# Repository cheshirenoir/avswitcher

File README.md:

# avswitcher
A modular AV Switcher. No scaling. Just switching. SVideo, Composite, Component and RGB (in the form of HD15)

THIS IS IN A VERY EARLY STATE. NOT FIT FOR PRODUCTION

This consists of a "Brainboard" containing an Arduino, A "Bus" that connects the other boards, and has the select logic for choosing which input has been selected, a control board, designed to plug into the front of the brain board. There is a Video out board that contains all the possible outputs, with a mirrored audio pair for each input. This plugs into the back of the Brainboard. It also handles the power in. (It's all designed to run off a 5V input. If I hit problems with power use, and I don't expect to, I can look at switching over to 9v and dropping a 7805 on each output board.) Finally there are the 4 different input boards that can be plugged into the bus, one each for SVideo, Composite, Component and "VGA" (Actually just RGBHV).
Each input board has a digitally controlled switch, which means unless they are selected, they stay isolated. Awesome for keeping the bus quiet when you are using the other input.
Why did I build this? Becauise I accidentally ended up with a collection of consoles, and switching between them was becoming a nightmare of switchers, scalers and general cable mess. I decided I wanted everything plugging into one box, and I could then plug just one scaler into each output.
I am now contemplating adding a relay to each output so I can switch on and off scalers as needed. That will need to wait for a later versions.

I haven't even started writing code for any of this. Talk about putting the horse before the cart.

Thanks to Kaypy for his advice.

Oh erm. CC-BY-SA

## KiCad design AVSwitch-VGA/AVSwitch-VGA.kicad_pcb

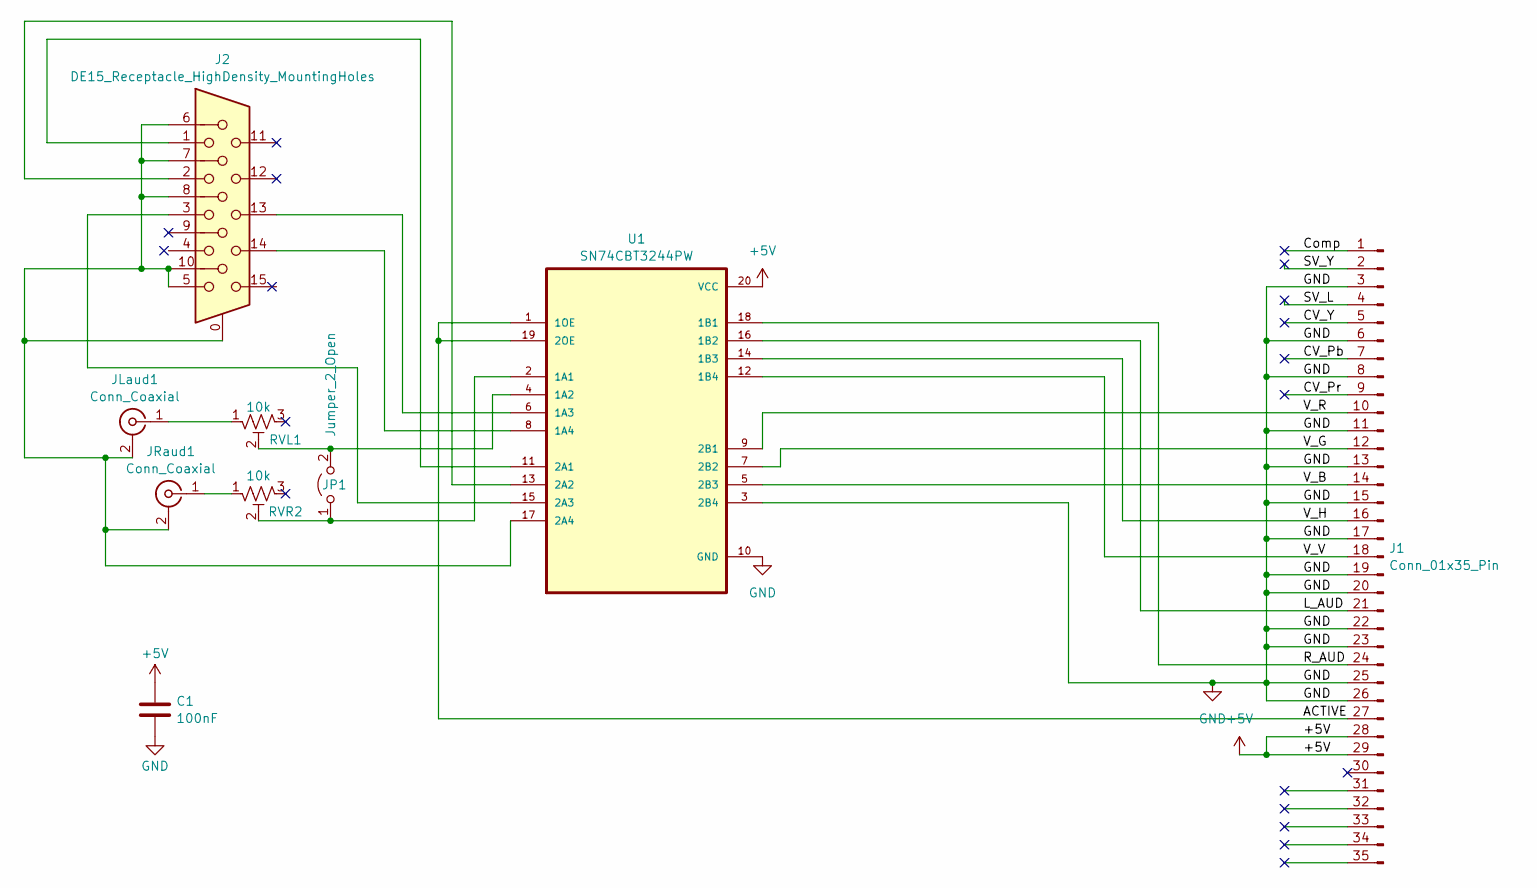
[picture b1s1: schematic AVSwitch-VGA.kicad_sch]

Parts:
C1: 100nF; C_Disc_D7.0mm_W2.5mm_P5.00mm
J1: Conn_01x35_Pin; PinSocket_1x35_P2.54mm_Vertical
J2: DE15_Receptacle_HighDensity_MountingHoles; DSUB-15-HD_Female_Horizontal_P2.29x1.98mm_EdgePinOffset3.03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
JLaud1: Conn_Coaxial; RCA Single (Altronics)
JP1: Jumper_2_Open; PinHeader_1x02_P2.54mm_Vertical
JRaud1: Conn_Coaxial; RCA Single (Altronics)
RVL1: 10k; TrimPot Vertical (Altronics)
RVR2: 10k; TrimPot Vertical (Altronics)
U1: SN74CBT3244PW; SOIC-20W_7.5x12.8mm_P1.27mm

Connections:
+5V: C1.1, J1.28, J1.29, U1.20 (VCC)
/ACTIVE: J1.27, U1.1 (1OE), U1.19 (2OE)
/CV_Pb: J1.7
/CV_Pr: J1.9
/CV_Y: J1.5
/Comp: J1.1
/L_AUD: J1.21, U1.16 (1B2)
/R_AUD: J1.24, U1.18 (1B1)
/SV_L: J1.4
/SV_Y: J1.2
/V_B: J1.14, U1.5 (2B3)
/V_G: J1.12, U1.7 (2B2)
/V_H: J1.16, U1.14 (1B3)
/V_R: J1.10, U1.9 (2B1)
/V_V: J1.18, U1.12 (1B4)
GND: C1.2, J1.3, J1.6, J1.8, J1.11, J1.13, J1.15, J1.17, J1.19, J1.20, J1.22, J1.23, J1.25, J1.26, U1.3 (2B4), U1.10 (GND)
unnamed: J2.0, J2.5, J2.6, J2.7, J2.8, J2.10, JLaud1.2 (Ext), JRaud1.2 (Ext), U1.17 (2A4)
unnamed: JLaud1.1 (In), RVL1.1
unnamed: JP1.1 (A), RVR2.2, U1.2 (1A1)
unnamed: JP1.2 (B), RVL1.2, U1.4 (1A2)
unnamed: JRaud1.1 (In), RVR2.1
unnamed: J2.13, U1.6 (1A3)
unnamed: J2.14, U1.8 (1A4)
unnamed: J2.1, U1.11 (2A1)
unnamed: J2.2, U1.13 (2A2)
unnamed: J2.3, U1.15 (2A3)

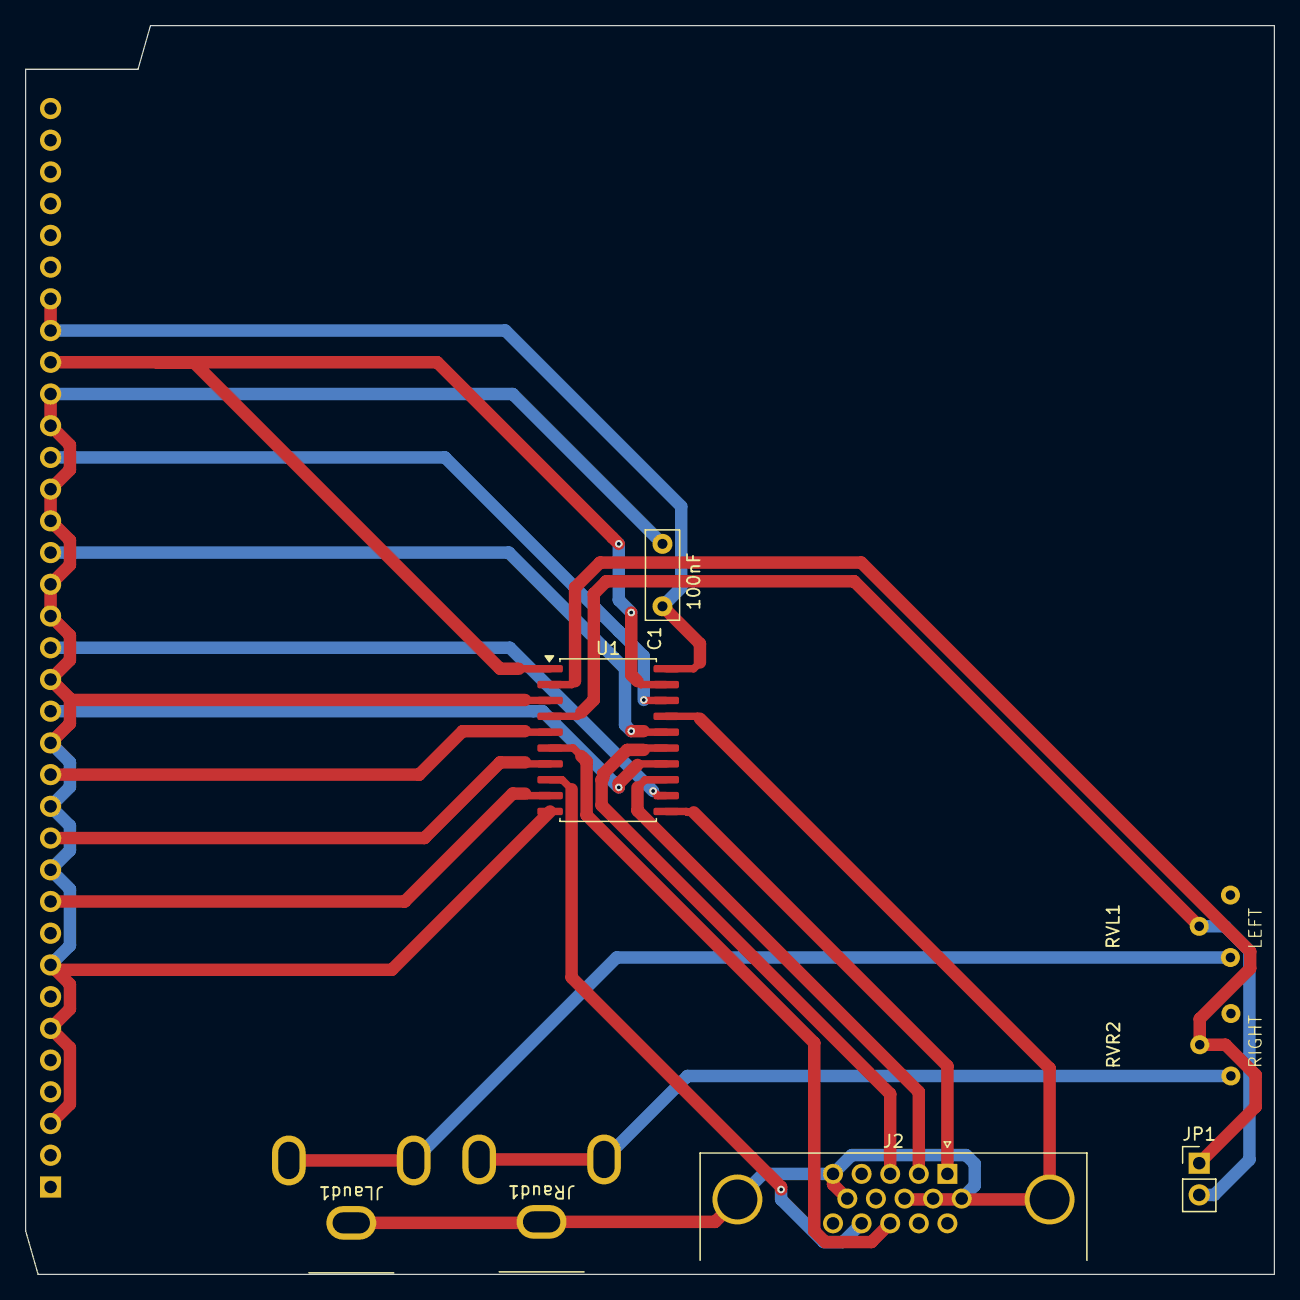
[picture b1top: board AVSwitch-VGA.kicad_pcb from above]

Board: 2 copper layers, 100.0 x 100.0 mm, 9 parts (1 on the bottom side), 20 nets.

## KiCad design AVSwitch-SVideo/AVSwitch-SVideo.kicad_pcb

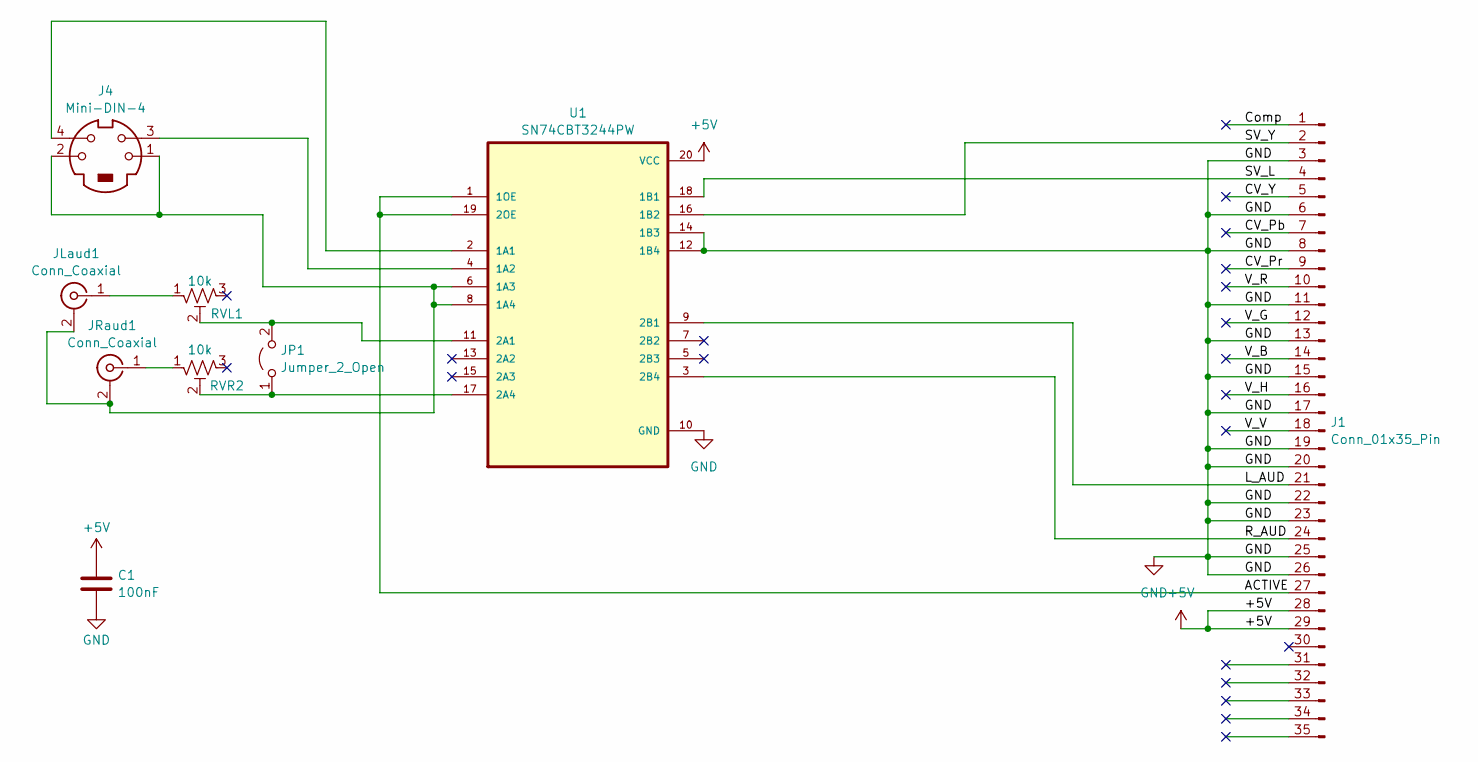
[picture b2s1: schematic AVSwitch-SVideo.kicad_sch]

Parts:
C1: 100nF; C_Disc_D7.0mm_W2.5mm_P5.00mm
J1: Conn_01x35_Pin; PinSocket_1x35_P2.54mm_Vertical
J4: Mini-DIN-4; Mini DIN 4 (Altronics)
JLaud1: Conn_Coaxial; RCA Single (Altronics)
JP1: Jumper_2_Open; PinHeader_1x02_P2.54mm_Vertical
JRaud1: Conn_Coaxial; RCA Single (Altronics)
RVL1: 10k; TrimPot Vertical (Altronics)
RVR2: 10k; TrimPot Vertical (Altronics)
U1: SN74CBT3244PW; SOIC-20W_7.5x12.8mm_P1.27mm

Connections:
+5V: C1.1, J1.28, J1.29, U1.20 (VCC)
/ACTIVE: J1.27, U1.1 (1OE), U1.19 (2OE)
/CV_Pb: J1.7
/CV_Pr: J1.9
/CV_Y: J1.5
/Comp: J1.1
/L_AUD: J1.21, U1.9 (2B1)
/R_AUD: J1.24, U1.3 (2B4)
/SV_L: J1.4, U1.18 (1B1)
/SV_Y: J1.2, U1.16 (1B2)
/V_B: J1.14
/V_G: J1.12
/V_H: J1.16
/V_R: J1.10
/V_V: J1.18
GND: C1.2, J1.3, J1.6, J1.8, J1.11, J1.13, J1.15, J1.17, J1.19, J1.20, J1.22, J1.23, J1.25, J1.26, U1.10 (GND), U1.12 (1B4), U1.14 (1B3)
unnamed: J4.1, J4.2, JLaud1.2 (Ext), JRaud1.2 (Ext), U1.6 (1A3), U1.8 (1A4)
unnamed: JLaud1.1 (In), RVL1.1
unnamed: JP1.1 (A), RVR2.2, U1.17 (2A4)
unnamed: JP1.2 (B), RVL1.2, U1.11 (2A1)
unnamed: JRaud1.1 (In), RVR2.1
unnamed: J4.4, U1.2 (1A1)
unnamed: J4.3, U1.4 (1A2)

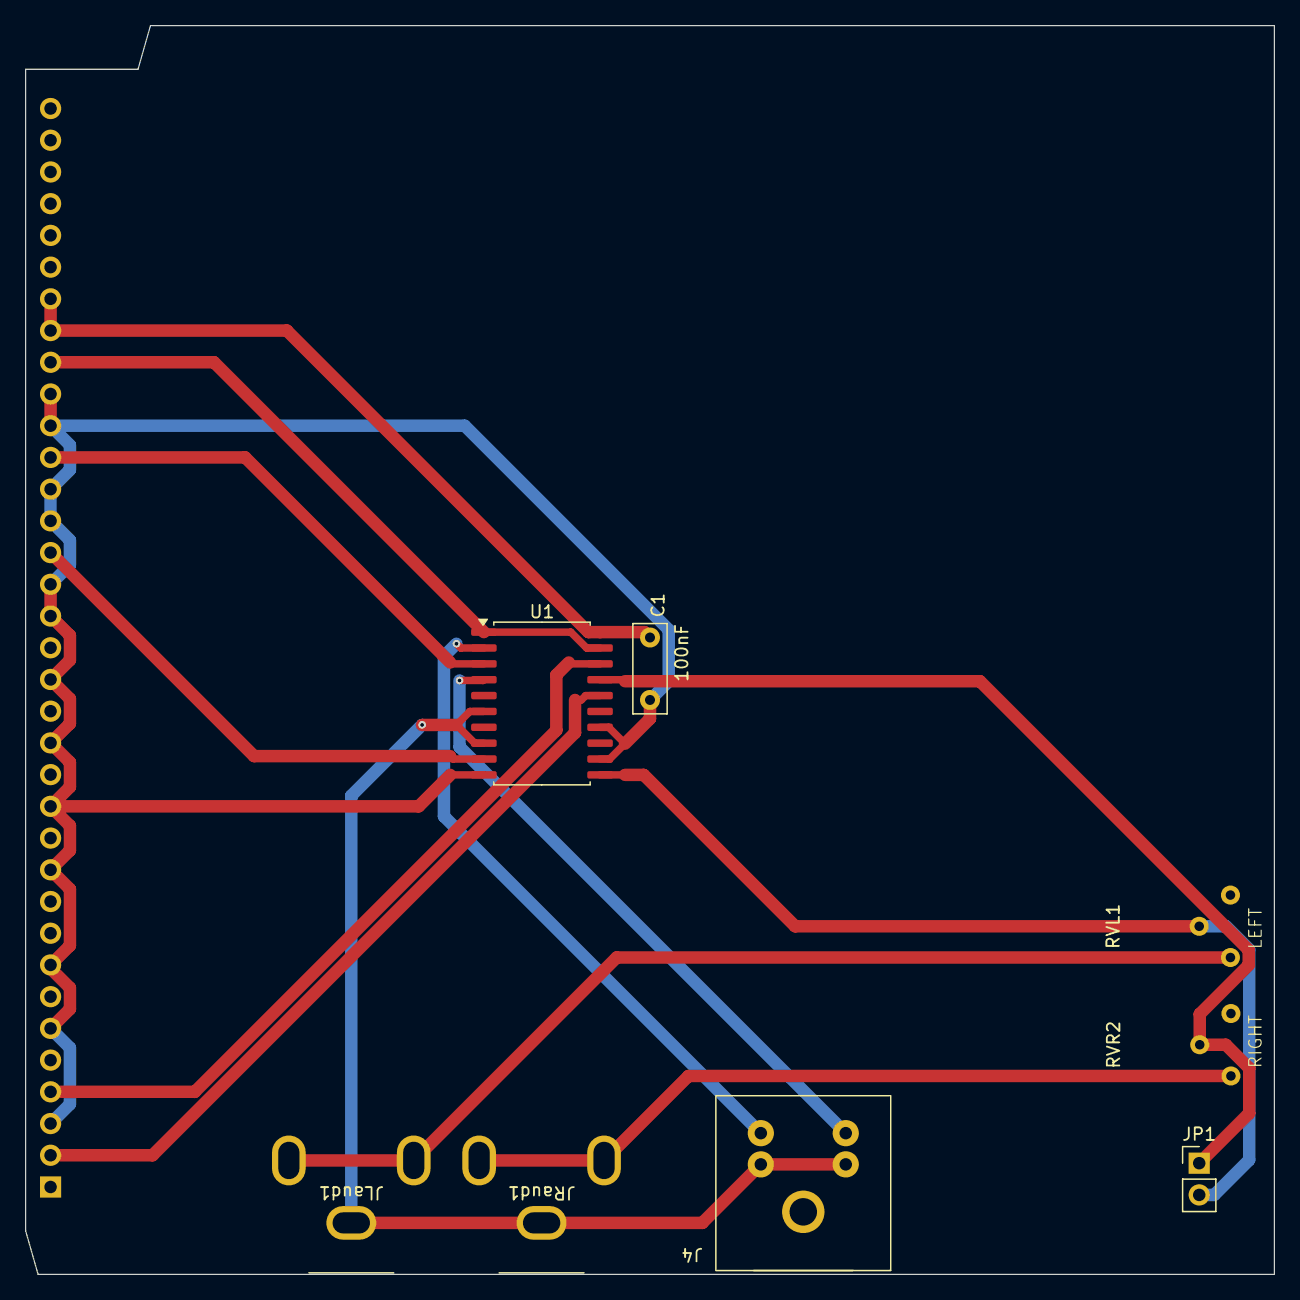
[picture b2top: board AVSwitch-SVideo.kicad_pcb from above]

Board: 2 copper layers, 100.0 x 100.0 mm, 9 parts (1 on the bottom side), 14 nets.

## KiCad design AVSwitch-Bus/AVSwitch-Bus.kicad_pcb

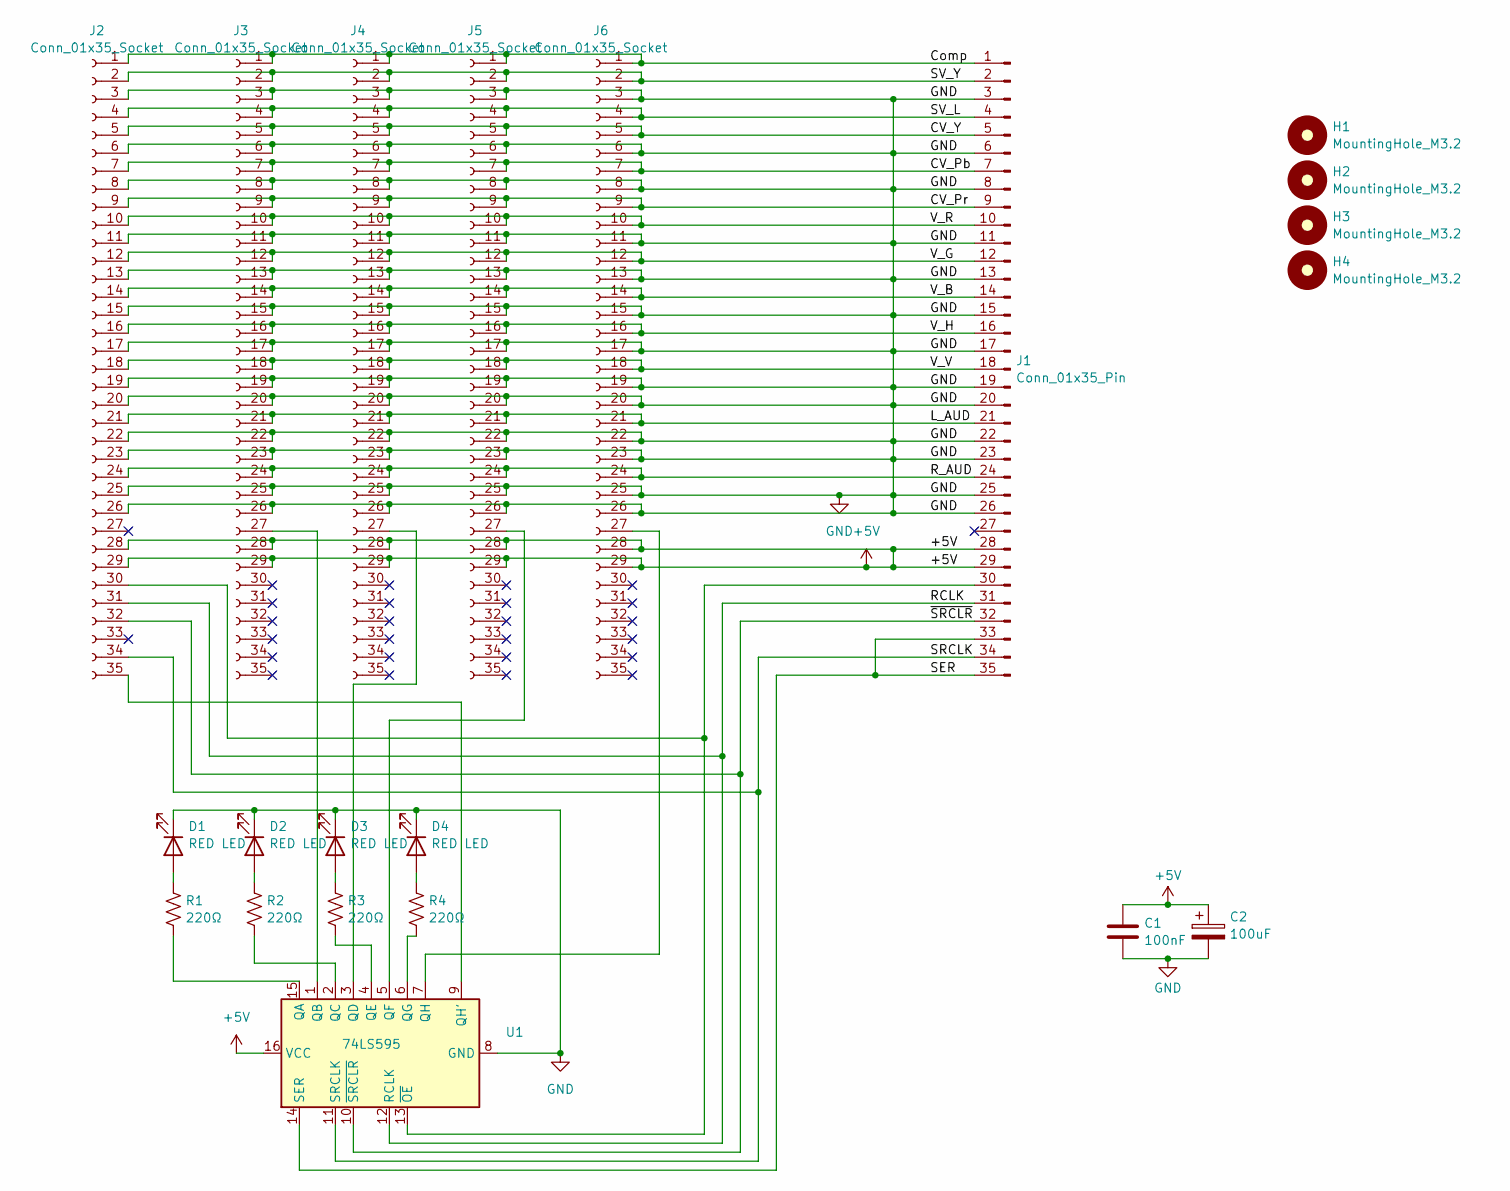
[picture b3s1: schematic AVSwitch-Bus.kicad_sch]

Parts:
C1: 100nF; C_Disc_D5.0mm_W2.5mm_P5.00mm
C2: 100uF; CP_Radial_D8.0mm_P3.50mm
D1, D2, D3, D4: RED LED; LED_D5.0mm
H1, H2, H3, H4: MountingHole_M3.2; MountingHole_3.2mm_M3_DIN965_Pad
J1: Conn_01x35_Pin; PinHeader_1x35_P2.54mm_Vertical
J2, J3, J4, J5, J6: Conn_01x35_Socket; PinSocket_1x35_P2.54mm_Vertical
R1, R2, R3, R4: 220Ω; R_Axial_DIN0204_L3.6mm_D1.6mm_P7.62mm_Horizontal
U1: 74LS595; DIP-16_W7.62mm_Socket_LongPads

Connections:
+5V: C1.1, C2.1, J1.28, J1.29, J2.28, J2.29, J3.28, J3.29, J4.28, J4.29, J5.28, J5.29, J6.28, J6.29, U1.16 (VCC)
/CV_Pb: J1.7, J2.7, J3.7, J4.7, J5.7, J6.7
/CV_Pr: J1.9, J2.9, J3.9, J4.9, J5.9, J6.9
/CV_Y: J1.5, J2.5, J3.5, J4.5, J5.5, J6.5
/Comp: J1.1, J2.1, J3.1, J4.1, J5.1, J6.1
/L_AUD: J1.21, J2.21, J3.21, J4.21, J5.21, J6.21
/RCLK: J1.31, J2.31, U1.12 (RCLK)
/R_AUD: J1.24, J2.24, J3.24, J4.24, J5.24, J6.24
/SER: J1.33, J1.35, U1.14 (SER)
/SRCLK: J1.34, J2.34, U1.11 (SRCLK)
/SV_L: J1.4, J2.4, J3.4, J4.4, J5.4, J6.4
/SV_Y: J1.2, J2.2, J3.2, J4.2, J5.2, J6.2
/V_B: J1.14, J2.14, J3.14, J4.14, J5.14, J6.14
/V_G: J1.12, J2.12, J3.12, J4.12, J5.12, J6.12
/V_H: J1.16, J2.16, J3.16, J4.16, J5.16, J6.16
/V_R: J1.10, J2.10, J3.10, J4.10, J5.10, J6.10
/V_V: J1.18, J2.18, J3.18, J4.18, J5.18, J6.18
/~SRCLR: J1.32, J2.32, U1.10 (~SRCLR)
GND: C1.2, C2.2, D1.1 (K), D2.1 (K), D3.1 (K), D4.1 (K), J1.3, J1.6, J1.8, J1.11, J1.13, J1.15, J1.17, J1.19, J1.20, J1.22, J1.23, J1.25, J1.26, J2.3, J2.6, J2.8, J2.11, J2.13, J2.15, J2.17, J2.19, J2.20, J2.22, J2.23, J2.25, J2.26, J3.3, J3.6, J3.8, J3.11, J3.13, J3.15, J3.17, J3.19, J3.20, J3.22, J3.23, J3.25, J3.26, J4.3, J4.6, J4.8, J4.11, J4.13, J4.15, J4.17, J4.19, J4.20, J4.22, J4.23, J4.25, J4.26, J5.3, J5.6, J5.8, J5.11, J5.13, J5.15, J5.17, J5.19, J5.20, J5.22, J5.23, J5.25, J5.26, J6.3, J6.6, J6.8, J6.11, J6.13, J6.15, J6.17, J6.19, J6.20, J6.22, J6.23, J6.25, J6.26, U1.8 (GND)
unnamed: D1.2 (A), R1.1
unnamed: D2.2 (A), R2.1
unnamed: D3.2 (A), R3.1
unnamed: D4.2 (A), R4.1
unnamed: J1.30, J2.30, U1.13 (~OE)
unnamed: J2.35, U1.9 (QH')
unnamed: J3.27, U1.1 (QB)
unnamed: J4.27, U1.3 (QD)
unnamed: J5.27, U1.5 (QF)
unnamed: J6.27, U1.7 (QH)
unnamed: R1.2, U1.15 (QA)
unnamed: R2.2, U1.2 (QC)
unnamed: R3.2, U1.4 (QE)
unnamed: R4.2, U1.6 (QG)

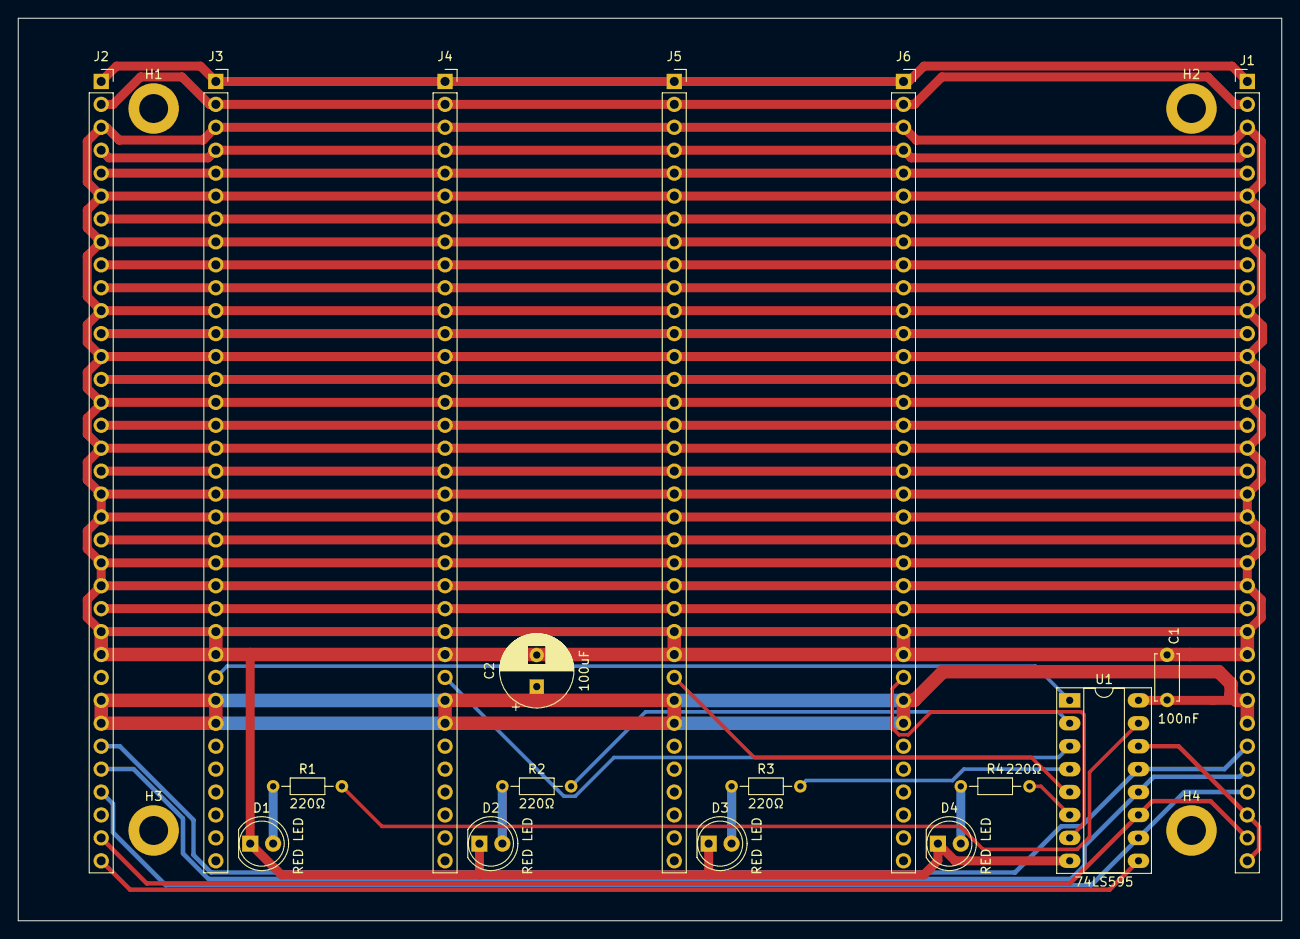
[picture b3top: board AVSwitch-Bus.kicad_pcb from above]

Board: 2 copper layers, 140.0 x 100.0 mm, 21 parts (0 on the bottom side), 33 nets.

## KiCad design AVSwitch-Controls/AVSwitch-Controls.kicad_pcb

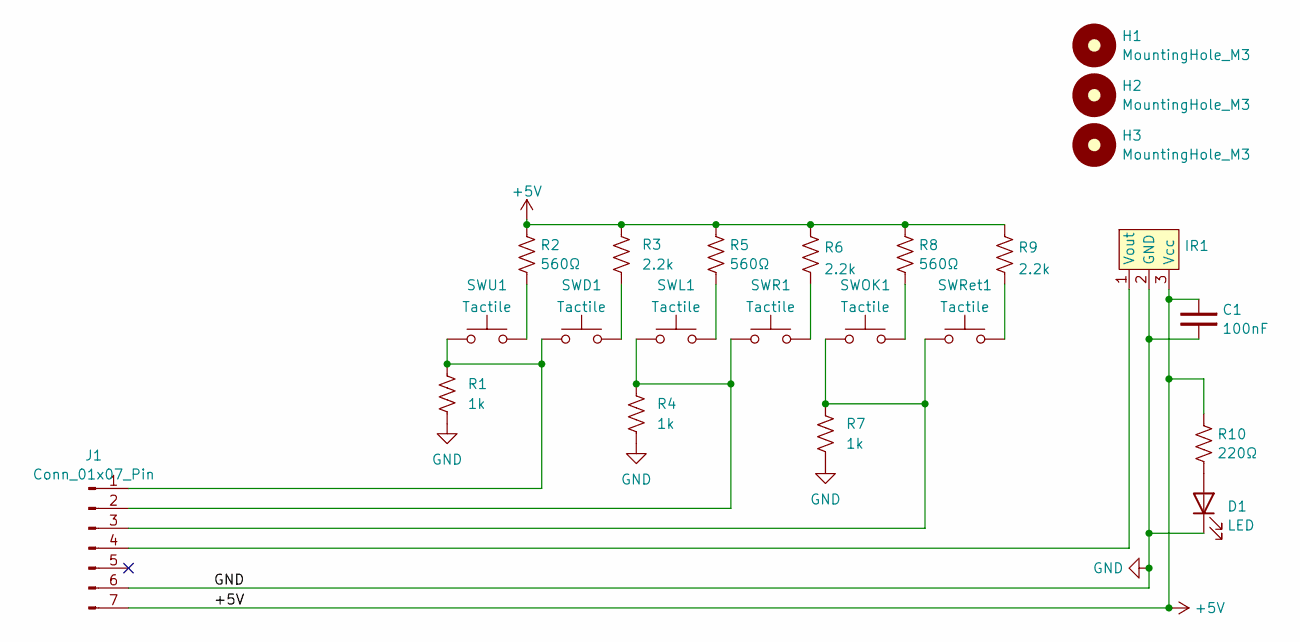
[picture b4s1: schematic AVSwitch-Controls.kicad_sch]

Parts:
C1: 100nF; C_Disc_D6.0mm_W2.5mm_P5.00mm
D1: LED; LED_D5.0mm
H1, H2, H3: MountingHole_M3; MountingHole_3.2mm_M3_DIN965_Pad
IR1: TO-220-3_Horizontal_TabDown
J1: Conn_01x07_Pin; PinHeader_1x07_P2.54mm_Vertical
R1, R4, R7: 1k; R_Axial_DIN0204_L3.6mm_D1.6mm_P7.62mm_Horizontal
R2, R5, R8: 560Ω; R_Axial_DIN0204_L3.6mm_D1.6mm_P7.62mm_Horizontal
R3, R6, R9: 2.2k; R_Axial_DIN0204_L3.6mm_D1.6mm_P7.62mm_Horizontal
R10: 220Ω; R_Axial_DIN0204_L3.6mm_D1.6mm_P7.62mm_Horizontal
SWD1: Tactile; DPadSwitch
SWL1: Tactile; DPadSwitch
SWOK1: Tactile; DPadSwitch
SWR1: Tactile; DPadSwitch
SWRet1: Tactile; SW_PUSH_4pin_6mm
SWU1: Tactile; DPadSwitch

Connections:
+5V: C1.1, IR1.3 (Vcc), J1.7, R2.1, R3.1, R5.1, R6.1, R8.1, R9.1, R10.1
GND: C1.2, D1.1 (K), IR1.2 (GND), J1.6, R1.2, R4.2, R7.2
unnamed: D1.2 (A), R10.2
unnamed: IR1.1 (Vout), J1.4
unnamed: J1.1, R1.1, SWD1.1 (A), SWD1.2 (A), SWU1.1 (A), SWU1.2 (A)
unnamed: J1.2, R4.1, SWL1.1 (A), SWL1.2 (A), SWR1.1 (A), SWR1.2 (A)
unnamed: J1.3, R7.1, SWOK1.1 (A), SWOK1.2 (A), SWRet1.1 (A), SWRet1.2 (A)
unnamed: R2.2, SWU1.3 (B), SWU1.4 (B)
unnamed: R3.2, SWD1.3 (B), SWD1.4 (B)
unnamed: R5.2, SWL1.3 (B), SWL1.4 (B)
unnamed: R6.2, SWR1.3 (B), SWR1.4 (B)
unnamed: R8.2, SWOK1.3 (B), SWOK1.4 (B)
unnamed: R9.2, SWRet1.3 (B), SWRet1.4 (B)

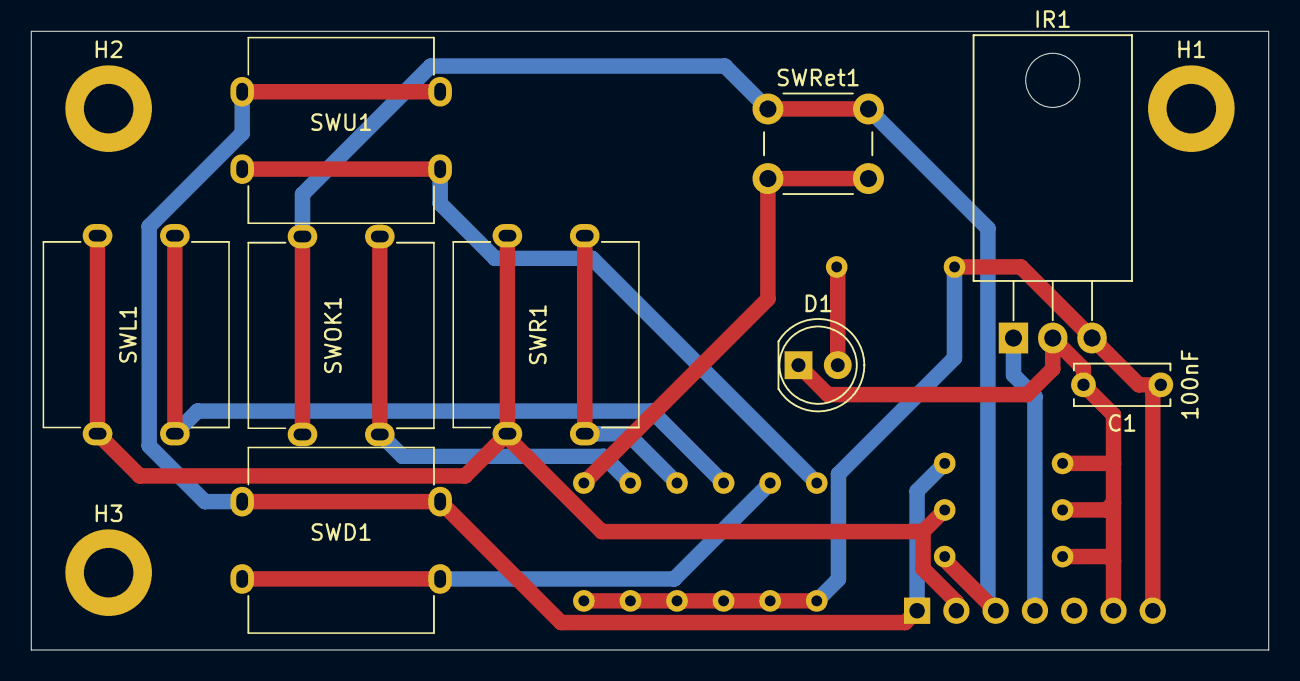
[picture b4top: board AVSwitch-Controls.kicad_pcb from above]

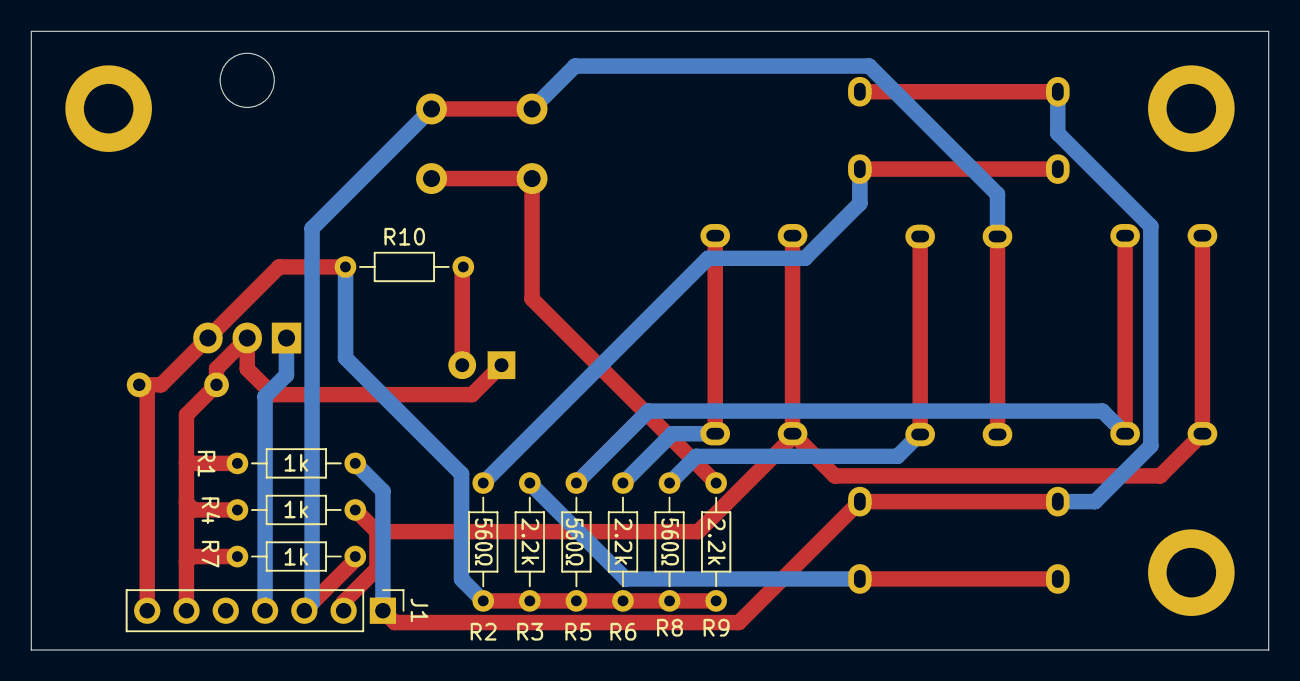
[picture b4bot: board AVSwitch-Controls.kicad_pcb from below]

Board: 2 copper layers, 80.0 x 40.0 mm, 23 parts (11 on the bottom side), 13 nets.

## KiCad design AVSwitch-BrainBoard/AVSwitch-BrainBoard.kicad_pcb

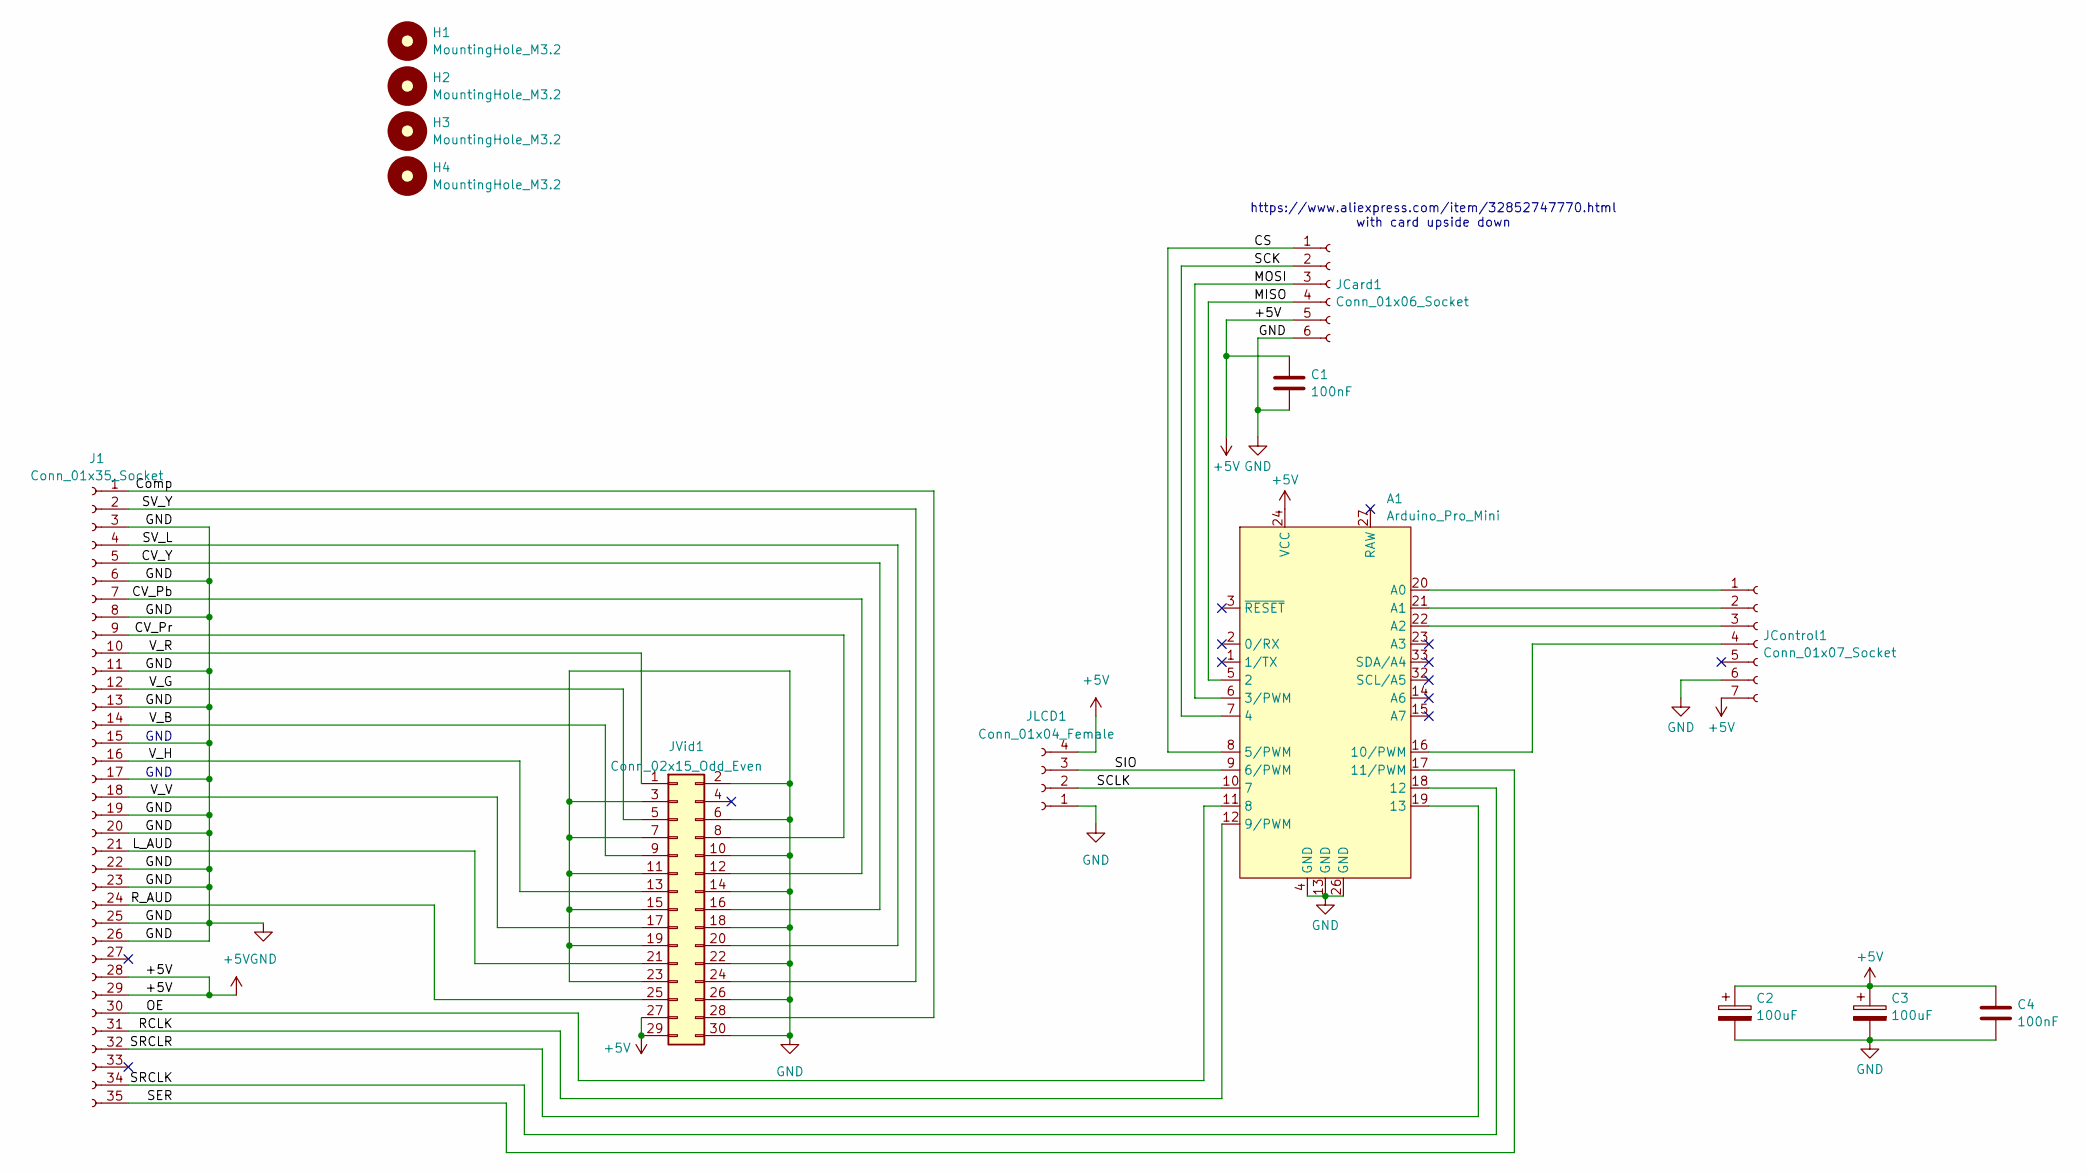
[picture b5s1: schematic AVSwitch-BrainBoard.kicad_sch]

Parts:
A1: Arduino_Pro_Mini; Arduino_pro_mini
C1, C4: 100nF; C_Disc_D5.0mm_W2.5mm_P5.00mm
C2, C3: 100uF; CP_Radial_D8.0mm_P3.50mm
H1, H2, H3, H4: MountingHole_M3.2; MountingHole_3.2mm_M3_DIN965_Pad
J1: Conn_01x35_Socket; PinSocket_1x35_P2.54mm_Vertical
JCard1: Conn_01x06_Socket; PinSocket_1x06_P2.54mm_Horizontal
JControl1: Conn_01x07_Socket; PinSocket_1x07_P2.54mm_Vertical
JLCD1: Conn_01x04_Female; PinSocket_1x04_P2.54mm_Vertical
JVid1: Conn_02x15_Odd_Even; PinHeader_2x15_P2.54mm_Vertical

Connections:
+5V: A1.24 (VCC), C1.2, C2.1, C3.1, C4.1, J1.28, J1.29, JCard1.5, JControl1.7, JLCD1.4, JVid1.27, JVid1.29
/CS: A1.8 (5/PWM), JCard1.1
/CV_Pb: J1.7, JVid1.12
/CV_Pr: J1.9, JVid1.8
/CV_Y: J1.5, JVid1.16
/Comp: J1.1, JVid1.28
/L_AUD: J1.21, JVid1.21
/MISO: A1.5 (2), JCard1.4
/MOSI: A1.6 (3/PWM), JCard1.3
/OE: A1.11 (8), J1.30
/RCLK: A1.12 (9/PWM), J1.31
/R_AUD: J1.24, JVid1.25
/SCK: A1.7 (4), JCard1.2
/SCLK: A1.10 (7), JLCD1.2
/SER: A1.17 (11/PWM), J1.35
/SIO: A1.9 (6/PWM), JLCD1.3
/SRCLK: A1.18 (12), J1.34
/SRCLR: A1.19 (13), J1.32
/SV_L: J1.4, JVid1.20
/SV_Y: J1.2, JVid1.24
/V_B: J1.14, JVid1.9
/V_G: J1.12, JVid1.5
/V_H: J1.16, JVid1.13
/V_R: J1.10, JVid1.1
/V_V: J1.18, JVid1.17
GND: A1.4 (GND), A1.13 (GND), A1.26 (GND), C1.1, C2.2, C3.2, C4.2, J1.3, J1.6, J1.8, J1.11, J1.13, J1.15, J1.17, J1.19, J1.20, J1.22, J1.23, J1.25, J1.26, JCard1.6, JControl1.6, JLCD1.1, JVid1.2, JVid1.3, JVid1.6, JVid1.7, JVid1.10, JVid1.11, JVid1.14, JVid1.15, JVid1.18, JVid1.19, JVid1.22, JVid1.23, JVid1.26, JVid1.30
unnamed: A1.16 (10/PWM), JControl1.4
unnamed: A1.20 (A0), JControl1.1
unnamed: A1.21 (A1), JControl1.2
unnamed: A1.22 (A2), JControl1.3

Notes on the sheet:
https://www.aliexpress.com/item/32852747770.html with card upside down
GND

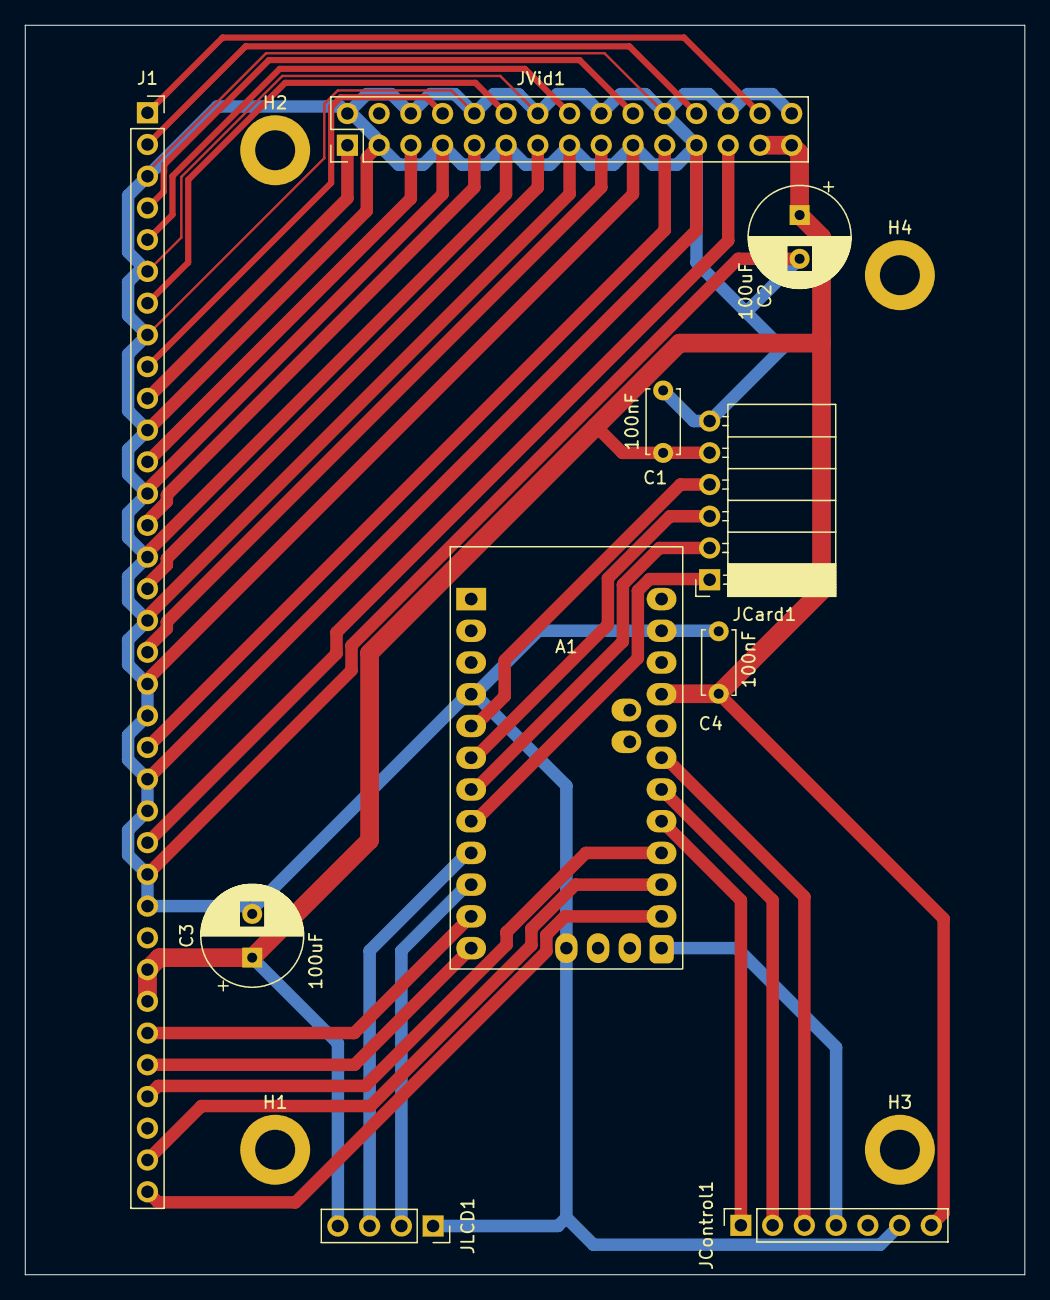
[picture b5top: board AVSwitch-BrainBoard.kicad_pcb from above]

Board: 2 copper layers, 80.0 x 100.0 mm, 14 parts (0 on the bottom side), 30 nets.
